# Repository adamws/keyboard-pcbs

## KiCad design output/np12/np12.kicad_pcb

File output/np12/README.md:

## np12/np12

[layout](np12-kle.json) - [PCB](np12.kicad_pcb)

{:loading="lazy"}

[Open in keyboard-layout-editor](http://www.keyboard-layout-editor.com/##@@_x:3;&=3,4;&@=0,0&=0,1&=0,2&=0,3;&@=1,0&=1,1&=1,2&=1,3;&@=2,0&=2,1&=2,2&=2,3)

{:loading="lazy"}

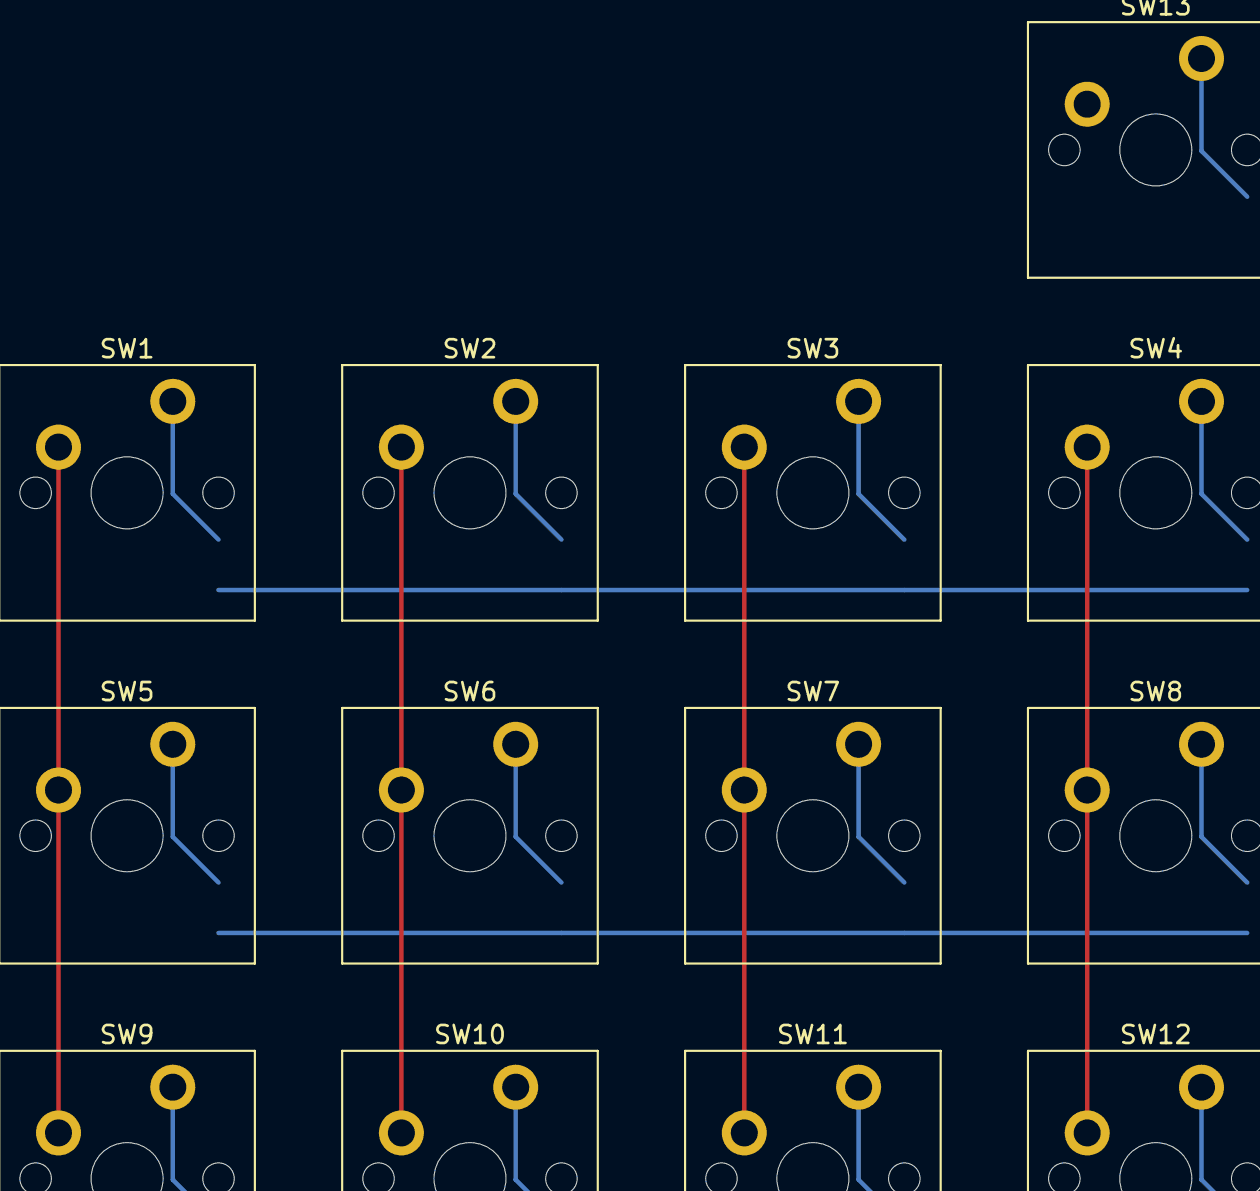
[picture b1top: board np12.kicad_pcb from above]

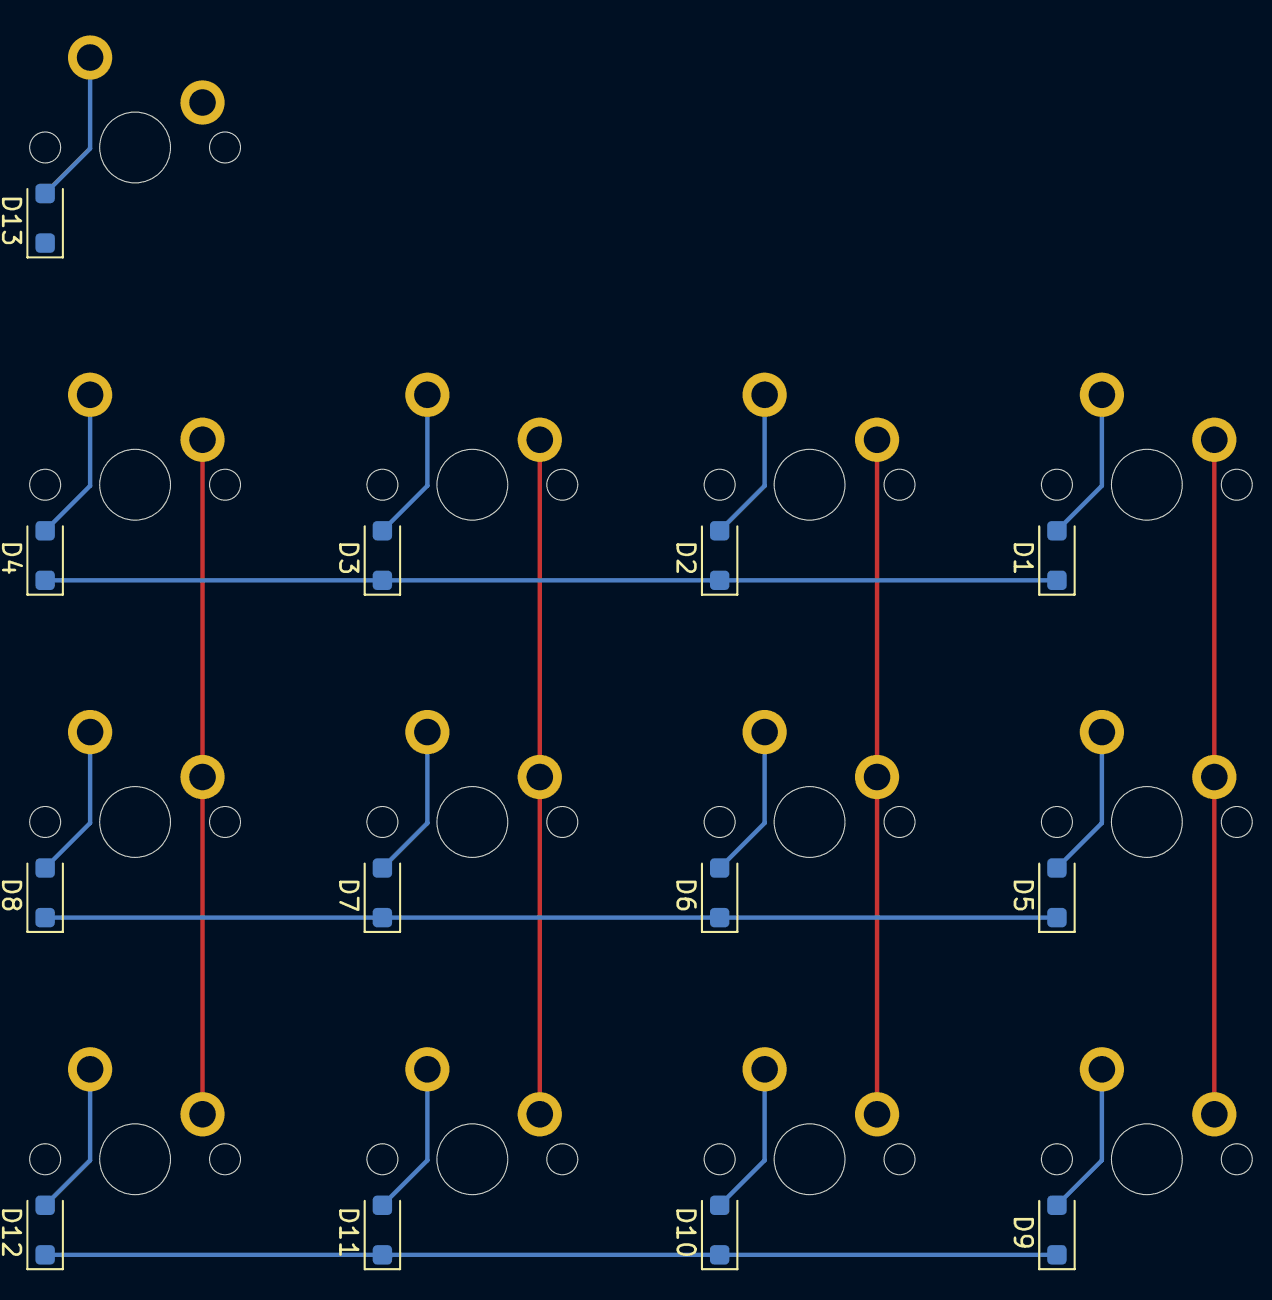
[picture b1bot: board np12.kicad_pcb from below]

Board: 2 copper layers, 26 parts (13 on the bottom side), 20 nets.

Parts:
D1, D2, D3, D4, D5, D6, D7, D8, D9, D10, D11, D12, D13: D_SOD-123F
SW1, SW2, SW3, SW4, SW5, SW6, SW7, SW8, SW9, SW10, SW11, SW12, SW13: SW_Cherry_MX_PCB_1.00u

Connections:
COL0: SW1.1, SW5.1, SW9.1
COL1: SW2.1, SW6.1, SW10.1
COL2: SW3.1, SW7.1, SW11.1
COL3: SW4.1, SW8.1, SW12.1
unnamed: D1.2, SW1.2
unnamed: D2.2, SW2.2
unnamed: D3.2, SW3.2
unnamed: D4.2, SW4.2
unnamed: D5.2, SW5.2
unnamed: D6.2, SW6.2
unnamed: D7.2, SW7.2
unnamed: D8.2, SW8.2
unnamed: D9.2, SW9.2
unnamed: D10.2, SW10.2
unnamed: D11.2, SW11.2
unnamed: D12.2, SW12.2
unnamed: D13.2, SW13.2
ROW0: D1.1, D2.1, D3.1, D4.1
ROW1: D5.1, D6.1, D7.1, D8.1
ROW2: D9.1, D10.1, D11.1, D12.1

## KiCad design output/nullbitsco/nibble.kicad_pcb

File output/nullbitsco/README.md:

## nullbitsco/nibble

[layout](nibble-kle.json) - [PCB](nibble.kicad_pcb)

{:loading="lazy"}

[Open in keyboard-layout-editor](http://www.keyboard-layout-editor.com/##@@_x:3.5&c=#777777;&=0,1&_c=#cccccc;&=0,2&=0,3&=0,4&=0,5&=0,6&=0,7&=0,8&=0,9&=0,10&=0,11&=0,12&=0,13&_c=#aaaaaa&w:2;&=0,14&_c=#777777;&=0,15;&@_x:2.5;&=1,0&_c=#aaaaaa&w:1.5;&=1,1&_c=#cccccc;&=1,2&=1,3&=1,4&=1,5&=1,6&=1,7&=1,8&=1,9&=1,10&=1,11&=1,12&=1,13&_c=#aaaaaa&w:1.5;&=1,14%0A%0A%0A3,0&_c=#777777;&=1,15;&@_x:2.5;&=2,0&_c=#aaaaaa&w:1.75;&=2,1&_c=#cccccc;&=2,2&=2,3&=2,4&=2,5&=2,6&=2,7&=2,8&=2,9&=2,10&=2,11&=2,12&_c=#aaaaaa&w:2.25;&=2,14%0A%0A%0A3,0&_c=#777777;&=2,15;&@_x:2.5;&=3,0&_c=#aaaaaa&w:2.25;&=3,1%0A%0A%0A4,0&_c=#cccccc;&=3,2&=3,3&=3,4&=3,5&=3,6&=3,7&=3,8&=3,9&=3,10&=3,11&_c=#aaaaaa&w:1.75;&=3,12&_c=#777777;&=3,14&=3,15;&@_x:2.5;&=4,0&_c=#aaaaaa&w:1.25;&=4,1%0A%0A%0A0,0&_w:1.25;&=4,2%0A%0A%0A0,0&_w:1.25;&=4,3%0A%0A%0A0,0&_c=#cccccc&w:6.25;&=4,6%0A%0A%0A1,0&_c=#aaaaaa;&=4,9%0A%0A%0A2,0&=4,10%0A%0A%0A2,0&=4,11%0A%0A%0A2,0&_c=#777777;&=4,12&=4,14&=4,15;&@_x:20.75&y:-4&w:1.25&h:2&w2:1.5&h2:1&x2:-0.25;&=2,14%0A%0A%0A3,1;&@_x:19.75&c=#cccccc;&=1,14%0A%0A%0A3,1;&@_c=#aaaaaa&w:1.25;&=3,1%0A%0A%0A4,1&=0,0%0A%0A%0A4,1;&@_x:3.5&y:1&w:1.5;&=4,1%0A%0A%0A0,1&_w:1.5;&=4,2%0A%0A%0A0,1&_x:0.75&c=#cccccc&w:2.75;&=4,6%0A%0A%0A1,1&_w:1.25;&=4,9%0A%0A%0A1,1&_w:2.25;&=4,6%0A%0A%0A1,1&_c=#aaaaaa&w:1.5;&=4,10%0A%0A%0A2,1&_w:1.5;&=4,11%0A%0A%0A2,1)

{:loading="lazy"}

## nullbitsco/scramble

[layout](scramble-kle.json) - [PCB](scramble.kicad_pcb)

{:loading="lazy"}

[Open in keyboard-layout-editor](http://www.keyboard-layout-editor.com/##@@_c=#777777;&=0,0&=0,1&=0,2;&@=1,0&=1,1&=1,2)

{:loading="lazy"}

## nullbitsco/snap

[layout](snap-kle.json) - [PCB](snap.kicad_pcb)

{:loading="lazy"}

[Open in keyboard-layout-editor](http://www.keyboard-layout-editor.com/##@@_x:3.5&y:1.25&c=#aaaaaa;&=0,1&=0,2&=0,3&=0,4&=0,5&=0,6&=0,7&=6,0&=6,1&=6,2&=6,3&=6,4&=6,5&=6,6&=6,7;&@_x:2.5&c=#777777;&=1,0%0A%0A%0A6,0%0A%0A%0A%0A%0A%0Ae0&_c=#cccccc;&=1,1&=1,2&=1,3&=1,4&=1,5&=1,6&=1,7&=7,0&=7,1&=7,2&=7,3&=7,4&=7,5&_c=#aaaaaa&w:2;&=7,6%0A%0A%0A5,0&_c=#777777;&=8,8%0A%0A%0A7,0%0A%0A%0A%0A%0A%0Ae1;&@_x:2.5;&=2,0&_c=#aaaaaa&w:1.5;&=2,1&_c=#cccccc;&=2,2&=2,3&=2,4&=2,5&=2,7&=8,0&=8,1&=8,2&=8,3&=8,4&=8,5&=8,6&_w:1.5;&=9,7%0A%0A%0A2,0&_c=#777777;&=8,7;&@_x:2.5;&=3,0&_c=#aaaaaa&w:1.75;&=3,1&_c=#cccccc;&=3,2&=3,3&=3,4&=3,5&=3,7&=9,0&=9,1&=9,2&=9,3&=9,4&=9,5&_c=#aaaaaa&w:2.25;&=9,6%0A%0A%0A2,0&_c=#777777;&=10,7;&@_x:2.5;&=4,0&_c=#aaaaaa&w:2.25;&=4,1%0A%0A%0A3,0&_c=#cccccc;&=4,3&=4,4&=4,5&=4,6&=4,7&=10,0&=10,1&=10,2&=10,3&=10,4&_c=#aaaaaa&w:1.75;&=10,5%0A%0A%0A4,0&_c=#777777;&=10,6%0A%0A%0A4,0&=11,7;&@_x:2.5;&=5,0&_c=#aaaaaa&w:1.25;&=5,1&_w:1.25;&=5,2&_w:1.25;&=5,3&_w:1.25;&=5,5%0A%0A%0A0,0&_w:2.25;&=5,7%0A%0A%0A0,0&_w:2.75;&=11,0&=11,1%0A%0A%0A1,0&=11,2%0A%0A%0A1,0&=11,3%0A%0A%0A1,0&_c=#777777;&=11,4%0A%0A%0A1,0&=11,5%0A%0A%0A1,0&=11,6;&@_x:16.5&y:-7.25&c=#cccccc;&=7,6%0A%0A%0A5,1&_c=#aaaaaa;&=7,7%0A%0A%0A5,1;&@_x:1.25&y:1.25;&=1,0%0A%0A%0A6,1&_x:17.5;&=8,8%0A%0A%0A7,1;&@_x:21.25&w:1.25&h:2&w2:1.5&h2:1&x2:-0.25;&=9,6%0A%0A%0A2,1;&@_x:20.25&c=#cccccc;&=9,7%0A%0A%0A2,1;&@_c=#aaaaaa&w:1.25;&=4,1%0A%0A%0A3,1&_c=#cccccc;&=4,2%0A%0A%0A3,1&_x:17.5&c=#aaaaaa&w:2.75;&=10,5%0A%0A%0A4,1;&@_x:7.25&y:1.25&w:2.25;&=5,5%0A%0A%0A0,1&_w:1.25;&=5,7%0A%0A%0A0,1&_x:2.75&w:1.25;&=11,1%0A%0A%0A1,1&_w:1.25;&=11,2%0A%0A%0A1,1&_w:1.25;&=11,4%0A%0A%0A1,1&_w:1.25;&=11,5%0A%0A%0A1,1)

{:loading="lazy"}

## nullbitsco/tidbit

[layout](tidbit-kle.json) - [PCB](tidbit.kicad_pcb)

{:loading="lazy"}

[Open in keyboard-layout-editor](http://www.keyboard-layout-editor.com/##@@_x:3.25;&=0,3&=0,4&=0,5;&@_x:2.25;&=1,2%0A%0A%0A2,0%0A%0A%0A%0A%0A%0Ae0&=1,3&_x:-1.0;&=1,3&=1,4&=1,5%0A%0A%0A0,0;&@_x:2.25;&=2,2%0A%0A%0A3,0%0A%0A%0A%0A%0A%0Ae1&=2,3&=2,4&=2,5%0A%0A%0A0,0;&@_x:2.25;&=3,2%0A%0A%0A4,0%0A%0A%0A%0A%0A%0Ae2&=3,3&=3,4&=3,5%0A%0A%0A1,0;&@_x:2.25;&=4,2%0A%0A%0A5,0&=4,3%0A%0A%0A5,0&=4,4&=4,5%0A%0A%0A1,0;&@_x:1&y:-4;&=1,2%0A%0A%0A2,1&_x:4.5&h:2;&=1,5%0A%0A%0A0,1;&@_x:1;&=2,2%0A%0A%0A3,1;&@_x:1;&=3,2%0A%0A%0A4,1&_x:4.5&h:2;&=3,5%0A%0A%0A1,1;&@_x:1;&=4,2%0A%0A%0A5,2%0A%0A%0A%0A%0A%0Ae3&=4,3%0A%0A%0A5,2;&@_x:2.25&y:0.25&w:2;&=4,2%0A%0A%0A5,1)

{:loading="lazy"}

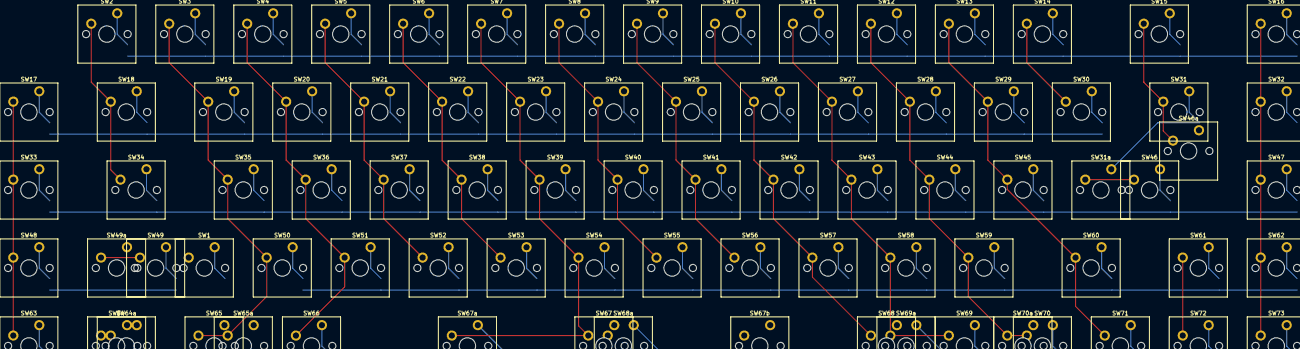
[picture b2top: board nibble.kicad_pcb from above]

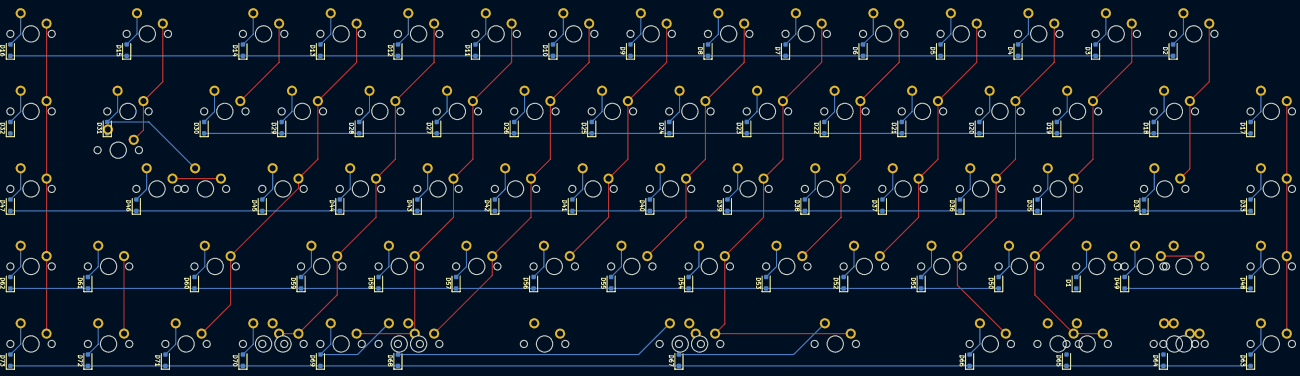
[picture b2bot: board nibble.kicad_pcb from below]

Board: 2 copper layers, 156 parts (73 on the bottom side), 94 nets.

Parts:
D1, D2, D3, D4, D5, D6, D7, D8, D9, D10, D11, D12, D13, D14, D15, D16, D17, D18, D19, D20, D21, D22, D23, D24, D25, D26, D27, D28, D29, D30, D31, D32, D33, D34, D35, D36, D37, D38, D39, D40, D41, D42, D43, D44, D45, D46, D47, D48, D49, D50, D51, D52, D53, D54, D55, D56, D57, D58, D59, D60, D61, D62, D63, D64, D65, D66, D67, D68, D69, D70, D71, D72, D73: D_SOD-123F
SW1, SW2, SW3, SW4, SW5, SW6, SW7, SW8, SW9, SW10, SW11, SW12, SW13, SW14, SW15, SW16, SW17, SW18, SW19, SW20, SW21, SW22, SW23, SW24, SW25, SW26, SW27, SW28, SW29, SW30, SW31, SW31a, SW32, SW33, SW34, SW35, SW36, SW37, SW38, SW39, SW40, SW41, SW42, SW43, SW44, SW45, SW46, SW46a, SW47, SW48, SW49, SW49a, SW50, SW51, SW52, SW53, SW54, SW55, SW56, SW57, SW58, SW59, SW60, SW61, SW62, SW63, SW64, SW64a, SW65, SW65a, SW66, SW67, SW67a, SW67b, SW68, SW68a, SW69, SW69a, SW70, SW70a, SW71, SW72, SW73: SW_Cherry_MX_PCB_1.00u

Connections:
COL0: SW1.1, SW17.1, SW33.1, SW48.1, SW63.1
COL1: SW2.1, SW18.1, SW34.1, SW49.1, SW49a.1, SW64.1, SW64a.1
COL2: SW3.1, SW19.1, SW35.1, SW50.1, SW65.1, SW65a.1
COL3: SW4.1, SW20.1, SW36.1, SW51.1, SW66.1
COL4: SW5.1, SW21.1, SW37.1, SW52.1
COL5: SW6.1, SW22.1, SW38.1, SW53.1
COL6: SW7.1, SW23.1, SW39.1, SW54.1, SW67.1, SW67a.1, SW67b.1
COL7: SW8.1, SW24.1, SW40.1, SW55.1
COL8: SW9.1, SW25.1, SW41.1, SW56.1
COL9: SW10.1, SW26.1, SW42.1, SW57.1, SW68.1, SW68a.1
COL10: SW11.1, SW27.1, SW43.1, SW58.1, SW69.1, SW69a.1
COL11: SW12.1, SW28.1, SW44.1, SW59.1, SW70.1, SW70a.1
COL12: SW13.1, SW29.1, SW45.1, SW60.1, SW71.1
COL13: SW14.1, SW30.1
COL14: SW15.1, SW31.1, SW31a.1, SW46.1, SW46a.1, SW61.1, SW72.1
COL15: SW16.1, SW32.1, SW47.1, SW62.1, SW73.1
unnamed: D1.2, SW1.2
unnamed: D2.2, SW2.2
unnamed: D3.2, SW3.2
unnamed: D4.2, SW4.2
unnamed: D5.2, SW5.2
unnamed: D6.2, SW6.2
unnamed: D7.2, SW7.2
unnamed: D8.2, SW8.2
unnamed: D9.2, SW9.2
unnamed: D10.2, SW10.2
unnamed: D11.2, SW11.2
unnamed: D12.2, SW12.2
unnamed: D13.2, SW13.2
unnamed: D14.2, SW14.2
unnamed: D15.2, SW15.2
unnamed: D16.2, SW16.2
unnamed: D17.2, SW17.2
unnamed: D18.2, SW18.2
unnamed: D19.2, SW19.2
unnamed: D20.2, SW20.2
unnamed: D21.2, SW21.2
unnamed: D22.2, SW22.2
unnamed: D23.2, SW23.2
unnamed: D24.2, SW24.2
unnamed: D25.2, SW25.2
unnamed: D26.2, SW26.2
unnamed: D27.2, SW27.2
unnamed: D28.2, SW28.2
unnamed: D29.2, SW29.2
unnamed: D30.2, SW30.2
unnamed: D31.2, SW31.2, SW31a.2
unnamed: D32.2, SW32.2
unnamed: D33.2, SW33.2
unnamed: D34.2, SW34.2
unnamed: D35.2, SW35.2
unnamed: D36.2, SW36.2
unnamed: D37.2, SW37.2
unnamed: D38.2, SW38.2
unnamed: D39.2, SW39.2
unnamed: D40.2, SW40.2
unnamed: D41.2, SW41.2
unnamed: D42.2, SW42.2
unnamed: D43.2, SW43.2
unnamed: D44.2, SW44.2
unnamed: D45.2, SW45.2
unnamed: D46.2, SW46.2, SW46a.2
unnamed: D47.2, SW47.2
unnamed: D48.2, SW48.2
unnamed: D49.2, SW49.2, SW49a.2
unnamed: D50.2, SW50.2
unnamed: D51.2, SW51.2
unnamed: D52.2, SW52.2
unnamed: D53.2, SW53.2
unnamed: D54.2, SW54.2
unnamed: D55.2, SW55.2
unnamed: D56.2, SW56.2
unnamed: D57.2, SW57.2
unnamed: D58.2, SW58.2
unnamed: D59.2, SW59.2
unnamed: D60.2, SW60.2
unnamed: D61.2, SW61.2
unnamed: D62.2, SW62.2
unnamed: D63.2, SW63.2
unnamed: D64.2, SW64.2, SW64a.2
unnamed: D65.2, SW65.2, SW65a.2
unnamed: D66.2, SW66.2
unnamed: D67.2, SW67.2, SW67a.2, SW67b.2
unnamed: D68.2, SW68.2, SW68a.2
unnamed: D69.2, SW69.2, SW69a.2
unnamed: D70.2, SW70.2, SW70a.2
unnamed: D71.2, SW71.2
unnamed: D72.2, SW72.2
unnamed: D73.2, SW73.2
ROW0: D1.1, D2.1, D3.1, D4.1, D5.1, D6.1, D7.1, D8.1, D9.1, D10.1, D11.1, D12.1, D13.1, D14.1, D15.1, D16.1
ROW1: D17.1, D18.1, D19.1, D20.1, D21.1, D22.1, D23.1, D24.1, D25.1, D26.1, D27.1, D28.1, D29.1, D30.1, D31.1, D32.1
ROW2: D33.1, D34.1, D35.1, D36.1, D37.1, D38.1, D39.1, D40.1, D41.1, D42.1, D43.1, D44.1, D45.1, D46.1, D47.1
ROW3: D48.1, D49.1, D50.1, D51.1, D52.1, D53.1, D54.1, D55.1, D56.1, D57.1, D58.1, D59.1, D60.1, D61.1, D62.1
ROW4: D63.1, D64.1, D65.1, D66.1, D67.1, D68.1, D69.1, D70.1, D71.1, D72.1, D73.1
